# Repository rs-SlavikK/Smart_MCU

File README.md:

# Smart W454 "W454-M" Upgrade Kit
Main Control Unit for my Smart W454's self made electronics system.

This repository includes both the ESP32's code from Visual Studio Code and the schematic + PCB from KiCAD

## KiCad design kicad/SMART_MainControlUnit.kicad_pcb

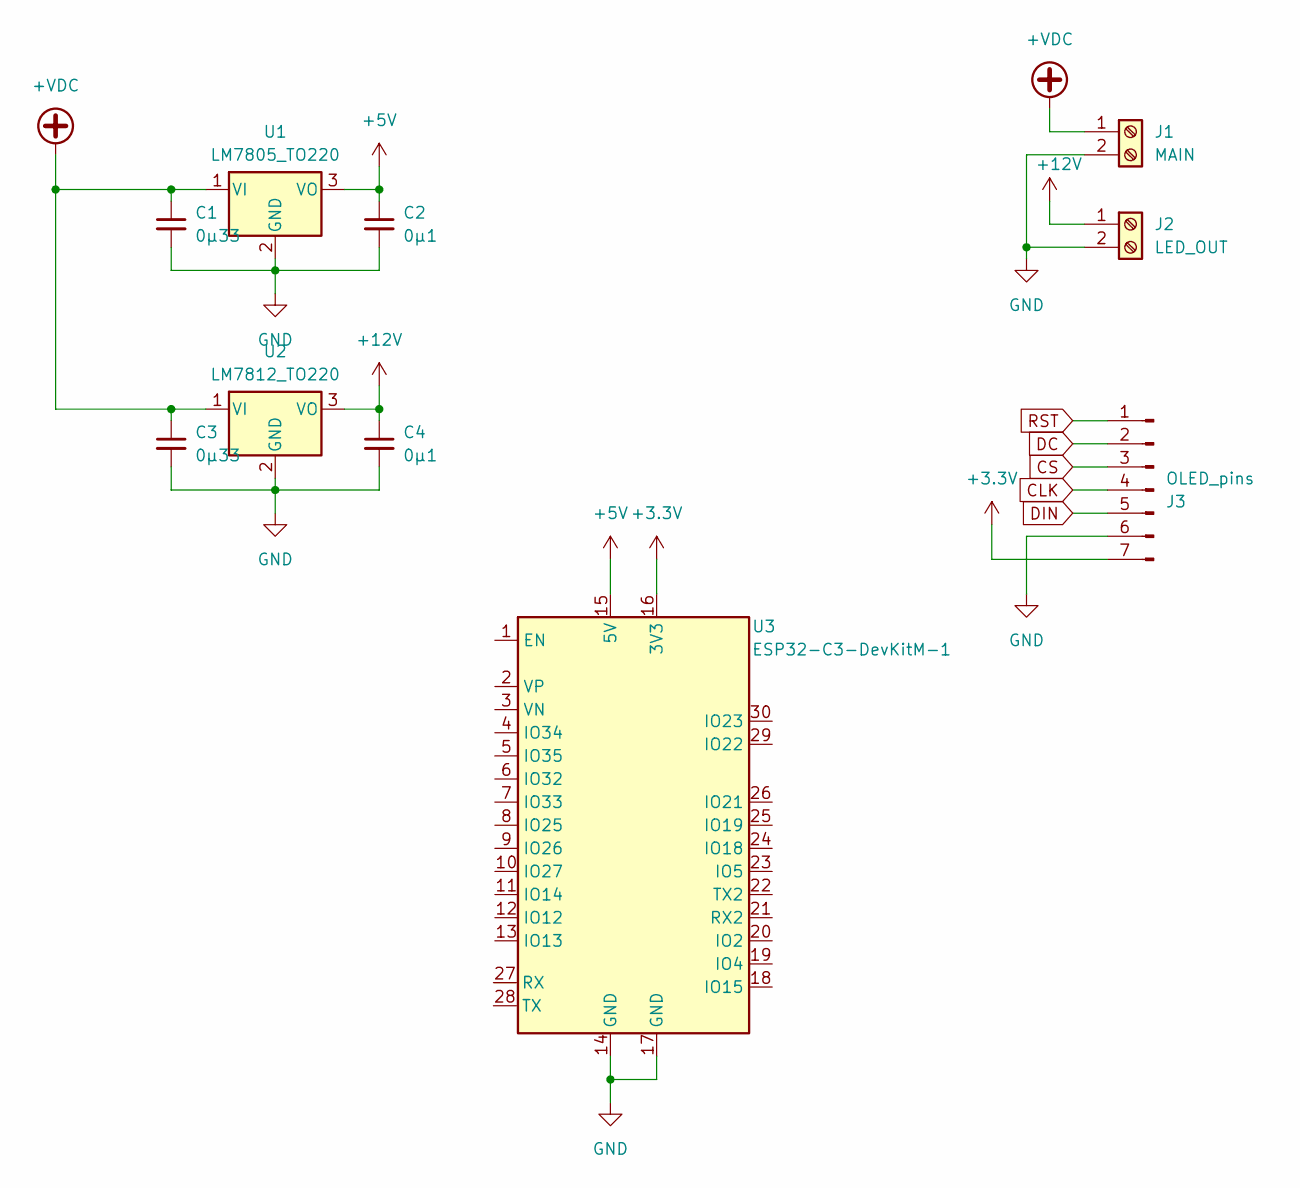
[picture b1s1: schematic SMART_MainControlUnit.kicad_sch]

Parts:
C1, C3: 0µ33; C_Disc_D5.0mm_W2.5mm_P5.00mm
C2, C4: 0µ1; C_Disc_D5.0mm_W2.5mm_P5.00mm
J1: MAIN; TerminalBlock_MaiXu_MX126-5.0-02P_1x02_P5.00mm
J2: LED_OUT; TerminalBlock_MaiXu_MX126-5.0-02P_1x02_P5.00mm
J3: OLED_pins; PinHeader_1x07_P2.54mm_Vertical
U1: LM7805_TO220; TO-220-3_Vertical
U2: LM7812_TO220; TO-220-3_Vertical
U3: ESP32-C3-DevKitM-1

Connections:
+3.3V: J3.7, U3.16 (3V3)
+5V: C2.1, U1.3 (VO), U3.15 (5V)
+12V: C4.1, J2.1, U2.3 (VO)
+VDC: C1.1, C3.1, J1.1, U1.1 (VI), U2.1 (VI)
CLK: J3.4
CS: J3.3
DC: J3.2
DIN: J3.5
GND: C1.2, C2.2, C3.2, C4.2, J1.2, J2.2, J3.6, U1.2 (GND), U2.2 (GND), U3.14 (GND), U3.17 (GND)
RST: J3.1

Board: 2 copper layers, 9 parts (0 on the bottom side), 5 nets, no tracks yet.

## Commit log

2025-01-29 setup
